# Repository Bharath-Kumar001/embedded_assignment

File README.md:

# Embedded Assignment – PCB Design & FreeRTOS

This repository includes:

1. **nPM1100 Evaluation Board** (PCB Design – KiCad 9)
2. **FreeRTOS Task Communication Example**
---
## 1. nPM1100 Evaluation Board

- Designed in **KiCad 9**
- 3.0V output, 200mA charge current
- 35mm x 35mm, all SMD components (top-mounted)

**Files:**
- `npm1100_eval_schematic.kicad_sch(schematic)
- `npm1100_eval_layout.kicad_pcb(PCB layout)
- `npm1100_eval_bom.csv`
## 2. FreeRTOS Task Example
Demonstrates task-to-task queue communication.
**Logic:**
- `Task1` sends (ID, value) every 500ms
- `Task2` acts based on value (kill/reset/boost priority)
**File:**
- `freertos_queue_example.c`
---
## Tools Used

- KiCad 9  
- FreeRTOS  
- SnapEDA (footprints)
---
## Author

**BharathKumar M**

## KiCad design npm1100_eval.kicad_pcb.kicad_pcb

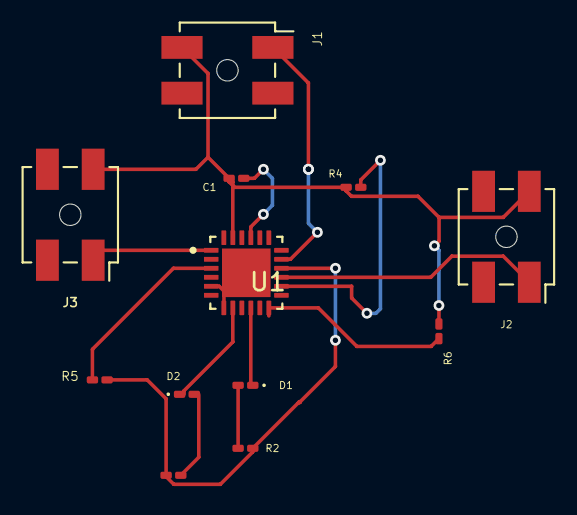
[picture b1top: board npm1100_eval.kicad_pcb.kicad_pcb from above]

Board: 2 copper layers, 12 parts (0 on the bottom side), 13 nets.

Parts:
C1: 10 µf; C_0201_0603Metric_Pad0.64x0.40mm_HandSolder
D1, D2: LED; LED_0201_0603Metric_Pad0.64x0.40mm_HandSolder
J1: Conn_01x02_pin; Samtec_HLE-102-02-xxx-DV-LC_2x02_P2.54mm_Horizontal
J2, J3: Conn_01x02_Pin; Samtec_HLE-102-02-xxx-DV-LC_2x02_P2.54mm_Horizontal
R1, R2, R5: 1K; R_0201_0603Metric_Pad0.64x0.40mm_HandSolder
R4: 10K; R_0201_0603Metric_Pad0.64x0.40mm_HandSolder
R6: 1.5K; R_0201_0603Metric_Pad0.64x0.40mm_HandSolder
U1: NPM1100-QDAB-R7; QFN50P400X400X90-25N

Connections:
/+: J2.1, U1.15 (VBAT)
/D1: R1.2, R2.2, R5.2, U1.16 (VSYS)
GND: C1.2, J1.2, J2.2, J3.2, R4.1, R6.1, U1.5 (ISET), U1.7 (MODE), U1.9 (VTERMSET), U1.23 (PVSS), U1.25 (EXP)
unnamed: D1.2 (A), R2.1
unnamed: D1.1 (K), U1.10 (ERR)
unnamed: D2.2 (A), R1.1
unnamed: D2.1 (K), U1.8 (CHG)
unnamed: J1.1, U1.17 (VBUS)
unnamed: J3.1, U1.1 (VOUTB)
unnamed: C1.1, U1.21 (DEC)
unnamed: R6.2, U1.12 (ICHG)
unnamed: R4.2, U1.14 (NTC)
unnamed: R5.1, U1.2 (VOUTBSET1), U1.3 (VOUTBSET2)

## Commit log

2025-06-17 Add files via upload
    This repo contain my assingment work for designing a simple evalution board using the Nordic nPM1100 PMIC. The board regulates 5V input down to 3V and also has charging capability for Li-ion battery 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
    assignmet__.kicad_sch – Schematic file
    asignment__.kicad_pcb – PCB layout file
    assignmet__.csv – BOM ( little incomplete)
2025-06-17 README.md
2025-06-17 Add files via upload
    This FreeRTOS example shows how two tasks talk using a queue.
    Task1 sends data (id & val) every 500ms.
    Task2 gets the data and reacts:
    id 0 → kills itself
    id 1:
    val 0 - boost its prio by 2 (only once) ,,val 1 - reset prio back if boosted,,val 2 -delete itself
